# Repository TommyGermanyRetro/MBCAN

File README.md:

# MBCAN

Herzlich willkommen auf meinen GITHUB-Seiten zum Projekt "MBCAN". Bis Ende 2025 hatte ich noch eine Website mit allen Infos rund um das Projekt. Die Pflege war aber mehr als aufwändig, und so habe ich sie geschlossen. Außerdem war das Projekt zu diesem Zeitpunkt bereits 18 Jahre alt. Also Zeit, es abzuschließen und Neues auszuprobieren.

Damit der letzte Stand der Unterlagen nicht verloren geht, habe ich:

1) Alle Unterlagen inkl. Quellcodes an Jörg Seitz übergeben (https://www.jss-elektronik.de)

2) Ein eigenes Git erstellt, auf dem die Downloads der ehemaligen Website abgelegt sind (<a href="https://github.com/TommyGermanyRetro/MBCAN/tree/main/Generation_3">Generation_3 hier im Git</a>)

Durch die Beschäftigung mit moderneren Prozessoren wie ESP32 und RP2040 habe ich neue Motivation für das Projekt gefunden und portiere gerade die 3. Generation Arduino IDE tauglich auf die Prozessoren ATMEGA644P (wie bei der 3. Generation), den ESP32-C3, den Waveshare RP2040 Zero und den RP RP2040 Pi Pico. Diese Versionen bezeichne ich als 4. Generation.

Passend gibt es ein erweitertes Parametriercenter, welches auch das Firmwareupdate der neuen Prozessoren über den CAN-Bus ermöglicht. Dazu wird die OTA-Funktionalität genutzt. Eine reale Umsetzung werde ich für den mbc80 mit dem ESP32-C3 in Eagle erstellen und gleichfalls hier posten. Nur die Bedienungsanleitungen und Warenkörbe, die ich früher mal geschrieben habe, wird es nicht mehr geben.

Solltet ihr Spaß an der Weiterentwicklung auf Basis dieser Sketche haben seid ihr gerne eingeladen, den Sourcecode fleißig zu nutzen und zu experimentieren.

Bleibt gesund,<br>
Thomas

## 1.  Systemarchitekur

Im folgenden Bild ist die Systemarchitektur von MBCAN abgebildet. Der CAN-Bus erfordert eine strikte Linienstruktur. Für Verzweigungen ist ein Hub notwendig zur Sicherstellung der Terminierung des Busses zur Vermeidung von ungewolltem Verhalten.

## 2.  Portierungshistorie

In der nachfolgenden Tabelle sind die bereits portierten (Generation_4/Module) UND getesteten Hardwareversionen und Sketches gelistet. D.h. die für die anderen Prozessoren erstellten Sketches sind Vorschläge ohne echte Überprüfung an einer Hardware. Die Spalte Android nennt Module, die als App auf einem Android-Tablet oder -Smartphone nachgebildet sind (Generation_4/Software/Android).

| Modultyp            | ATMEGA644P          | ESP32C3             | Android             |
| :-----------------: | :-----------------: | :-----------------: | :-----------------: |
| mbc-80              | HW:21-10-01         | HW:26-08-05         |                     |
| mbc-81              | HW:18-02-12<br>HW:24-01-06         |    |                     |
| mbc-82              | HW:21-03-01         |                     |                     |
| mbc-83              | HW:18-02-10<br>HW:24-03-23         |     |                     |
| mbc-84              | HW:18-02-03<br>HW:24-01-06         |      |                     |
| mbc-88              | HW:18-03-29<br>HW:24-01-06         |       |                     |
| mbc-89              | HW:22-03-01         |                     | [mbc89-APP](Generation_4/Software/Android/mbc89_APP) |
| mbc-90              | HW:18-03-04<br>HW:23-11-25         |                     |                     |
| mbc-91              | HW:16-10-02<br>HW:24-04-01         |                     |                     |
| mbc-92              | HW:24-07-20         |                     |                     |
| mbc-93              | HW:24-05-01         |                     |                     |

## 3.  Parametrierungscenter und Tools

Die Module müssen grundsätzlich durch das <b>Parametriercenter</b> basisparametriert werden. Dies bezieht sich auf die GUiD und den Kenner (Abweichungen sind in den Libs beschrieben). Danach ist eine Parametrierung über eine CSx möglich.

Als weiteres Tool steht ein TCP/CAN-Monitor zum Mitlesen auf dem CAN-Bus zur Verfügung.

Beide Tools liegen als Projektmappen in Generation_4/Software/Tools zum Download bereit.
	
## 4.  Lizenz

Soweit nicht ausdrücklich anders angegeben, gelten für dieses Repository folgende Lizenzen (Einzelheiten in [LICENSE.txt](LICENSE.txt)):

| Inhalt | Lizenz |
| --- | --- |
| Software: Sketches, Bibliotheken, Firmware, HEX-Dateien, Parametriercenter, CANMON | [MIT](LICENSE.txt) |
| Hardware: Schaltpläne und Layouts (Eagle), Gerber- und Bohrdaten, Stücklisten, 3D-Druck-Dateien | [CERN-OHL-S-2.0](LICENSE-CERN-OHL-S-2.0.txt) |
| Dokumentation und Bilder: READMEs, Bedienungsanleitungen, Übersichten, Flyer, Fotos | [CC BY-SA 4.0](https://creativecommons.org/licenses/by-sa/4.0/legalcode.de) |

Fremdbestandteile (MightyCore-Dateien, die 8x8-Zeichensatztabelle des SSD1306-Treibers, Arduino-Kerne in den HEX-Dateien) behalten ihre eigenen Lizenzen. Märklin, Central Station, Connect 6021 und Mobile Station sind Marken ihrer Inhaber; MBCAN ist kein Produkt dieser Firmen.

**Haftungsausschluss:** Alle Inhalte dieses Repositorys werden ohne Mängelgewähr ("wie besehen") und ohne jede Gewährleistung bereitgestellt. Nachbau, Anschluss und Nutzung der Hardware und Software erfolgen auf eigene Gefahr. Soweit gesetzlich zulässig, übernimmt der Autor keine Haftung für Schäden an Modellbahnanlagen, Zentralen, Decodern, Fahrzeugen, Rechnern, sonstigen Geräten oder Daten sowie für sonstige Verluste, die aus der Nutzung entstehen. Die Haftungsausschlüsse in [LICENSE.txt](LICENSE.txt) und [LICENSE-CERN-OHL-S-2.0.txt](LICENSE-CERN-OHL-S-2.0.txt) gelten uneingeschränkt.

# Tagebuch

## 07.11.2026

Neu: **mbc89-APP** für Android (Version 1.0.0) unter Generation_4/Software/Android/mbc89_APP mit Quellcode, fertiger APK und Anleitung. Die App bildet das mbc-89 mit Control Unit 6021, Control 80f, Keyboard 6040 und Memory 6043 auf Tablet oder Smartphone nach und verbindet sich per WLAN über einen mbc-80 (ESP32-C3) mit dem CAN-Bus. Hardwaregetestet an einer CS3, auch mit zwei Geräten gleichzeitig.

MBCANLib 1.1.2 / Mbc89Lib 1.1.1: CAN-Hash nach CS2-Protokoll 2.0 (bisher bekamen Module derselben Art mit Modulnummer #0/#1 denselben Hash). `MbcWifiBridge` sendet nicht mehr blockierend und trennt einen Client, der nichts mehr annimmt, statt durch den Watchdog neu zu starten. Hardwaregetestet mit dem mbc-80 ESP32-C3.

## 04.11.2026

MBCANLib/Mbc80Lib 1.1.1, mbc-80 ESP32-C3 V1.0.2: Nicht blockierender TWAI-Versand (`MbcCan`-Parameter `nonBlockingTx`, nur beim mbc-80 gesetzt). Damit meldet sich ein Android-Tablet-Modul über die CAN-TCP-Bridge des mbc-80 auch ohne MBCAN-Teilnehmer an der CS3 mit allen 76 Konfigkanälen an; vorher bremste der blockierende Versand die Bridge. Hardwaregetestet.

## 03.11.2026

MBCANLib/Mbc80Lib 1.1.0, mbc-80 ESP32-C3 V1.0.1: `MbcWifiBridge` nimmt bis zu 3 TCP-Clients gleichzeitig an, z. B. Parametriercenter und Android-Tablet am selben mbc-80. WLAN-Setup-Webportal zentriert. Hardwaregetestet.

## 02.11.2026

Haftungsausschluss im Abschnitt Lizenz ergänzt.

## 22.09.2026

mbc-80 ESP32-C3 (HW:26-08-05) hardwaregetestet und in der Tabelle ergänzt. Außerdem funktioniert das Firmwareupdate per OTA für den ESP32-C3 zuverlässig.

## 31.08.2026

Module mbc82, mbc89 und mbc93 ergänzt. BugFixes und RAM-Optimierung bei den anderen Modulen vorgenommen. 

## 23.08.2026

Unterstützte Hardwareversionen, Bedienungsanleitungen, Informations-MD und portierte Software unter Generation_4 hochgeladen

## 16.08.2026

Erste Bedienungsanleitungen zum neuen Parametriercenter und der portierten Module hochgeladen unter Generation_4/Dokumente

## 13.08.2026

Systemarchitekur ergänzt, Parametriercenter-ZIP unter 3. Generation ergänzt

## 09.08.2026

Neuanlage des Gits zum MBCAN-Projekt

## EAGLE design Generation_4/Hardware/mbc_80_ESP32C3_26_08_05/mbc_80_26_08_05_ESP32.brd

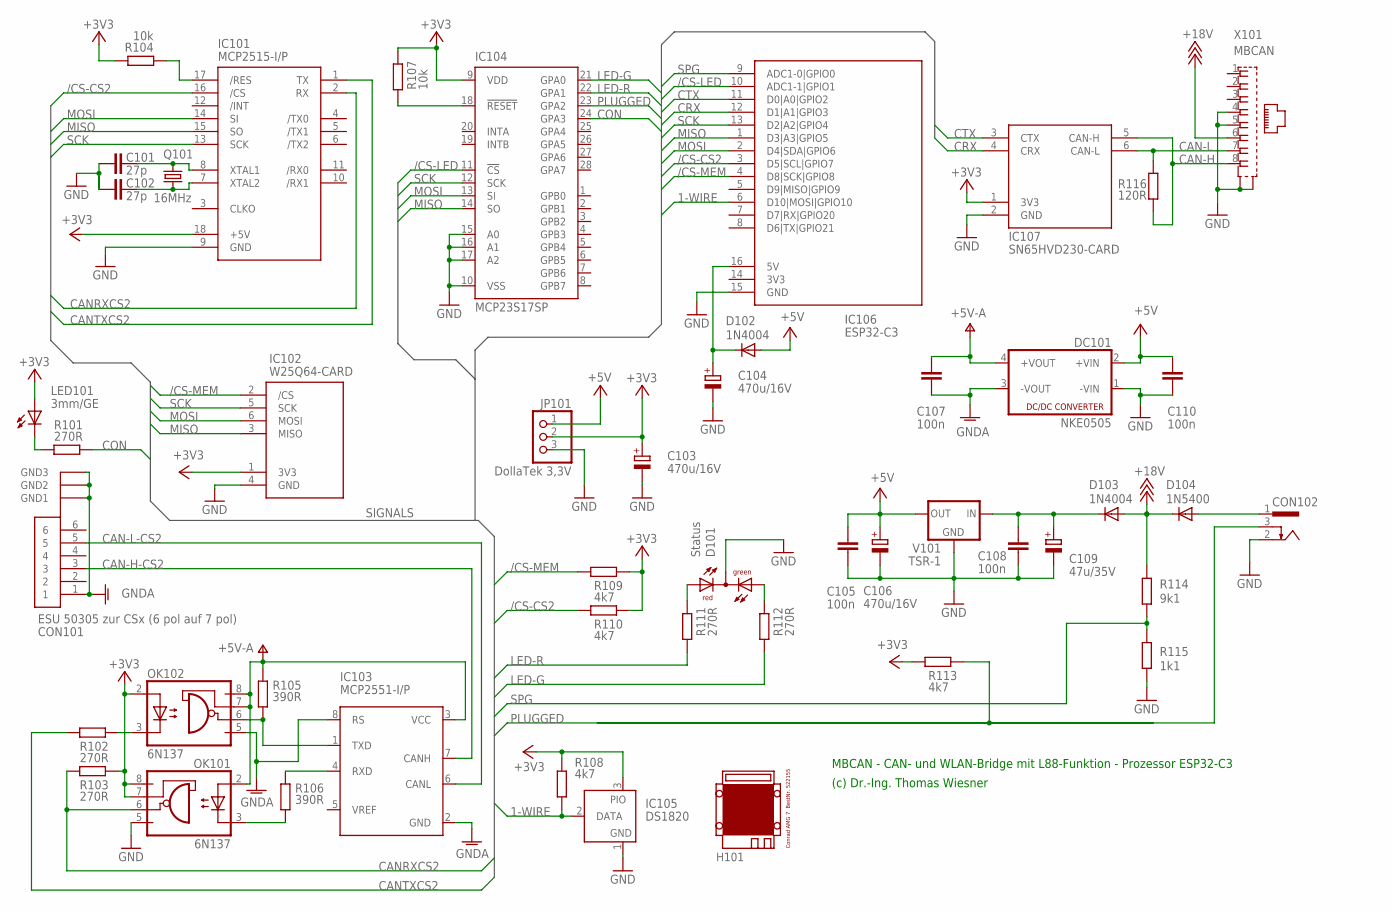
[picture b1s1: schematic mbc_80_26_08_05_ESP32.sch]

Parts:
C101, C102: 27p; C025-025X050
C103, C104, C106: 470u/16V; E3,5-8
C105, C107, C108, C110: 100n; C025-025X050
C109: 47u/35V; E2,5-7
CON101: ESU 50305 zur CSx (6 pol auf 7 pol); MINI-DIN-6-POL
CON102: POWER-JACK
D101: Status; DUOLED5MM
D102, D103: 1N4004; DO41-10
D104: 1N5400; DO201-15
DC101: NKE0505; NME
H101: MODULGEHÄUSE-AMG-7
IC101: MCP2515-I/P; DIL18
IC102: W25Q64-CARD; W25Q64CARD
IC103: MCP2551-I/P; DIL08
IC104: MCP23S17SP; DIL28-3
IC105: DS1820; TO92-
IC106: ESP32-C3
IC107: SN65HVD230-CARD
JP101: DollaTek 3,3V; 1X03
LED101: 3mm/GE; LED3MM
OK101, OK102: 6N137; DIL08
Q101: 16MHz; HC49U-V
R101, R102, R103, R111, R112: 270R; 0207/10
R104, R107: 10k; 0207/10
R105, R106: 390R; 0207/10
R108, R109, R110, R113: 4k7; 0207/10
R114: 9k1; 0207/10
R115: 1k1; 0207/10
R116: 120R; 0207/10
V101: TSR-1; TRACO-TSR-1
X101: MBCAN; 0446200002

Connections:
1-WIRE: IC105.2 (DATA), IC106.6 (D10|MOSI|GPIO10), R108.1
+3V3: C103.+, IC101.18 (+5V), IC102.1 (3V3), IC104.9 (VDD), IC105.3 (PIO), IC107.1 (3V3), JP101.2, LED101.A, OK101.7 (VE), OK101.8 (VCC), OK102.2 (A), R103.2, R104.1, R107.1, R108.2, R109.2, R110.2, R113.1
+5V: C105.1, C106.+, C110.1, D102.A, DC101.2 (+VIN), JP101.1, V101.OUT
+5V-A: C107.1, DC101.4 (+VOUT), IC103.3 (VCC), OK101.2 (A), OK102.7 (VE), OK102.8 (VCC), R105.2
+18V: D103.A, D104.C, R114.1, X101.6
/CS-CS2: IC101.16 (/CS), IC106.3 (D5|SCL|GPIO7), R110.1
/CS-LED: IC104.11 (!CS), IC106.10 (ADC1-1|GPIO1)
/CS-MEM: IC102.2 (/CS), IC106.4 (D8|SCK|GPIO8), R109.1
CAN-H: IC107.5 (CAN-H), R116.1, X101.8
CAN-H-CS2: CON101.3, IC103.7 (CANH)
CAN-L: IC107.6 (CAN-L), R116.2, X101.7
CAN-L-CS2: CON101.5, IC103.6 (CANL)
CANRXCS2: IC101.2 (RX), OK101.6 (VO), R103.1
CANTXCS2: IC101.1 (TX), R102.2
CON: IC104.24 (GPA3), R101.1
CRX: IC106.12 (D1|A1|GPIO3), IC107.4 (CRX)
CTX: IC106.11 (D0|A0|GPIO2), IC107.3 (CTX)
GND: C101.2, C102.2, C103.-, C104.-, C105.2, C106.-, C108.2, C109.-, C110.2, CON102.2, D101.K (C), DC101.1 (-VIN), IC101.9 (GND), IC102.4 (GND), IC104.10 (VSS), IC104.15 (A0), IC104.16 (A1), IC104.17 (A2), IC105.1 (GND), IC106.15 (GND), IC107.2 (GND), JP101.3, OK101.5 (GND), R115.2, V101.GND, X101.4, X101.5, X101.S@1 (S1), X101.S@2 (S2)
GNDA: C107.2, CON101.1, CON101.A1 (GND1), CON101.A2 (GND2), CON101.A3 (GND3), DC101.3 (-VOUT), IC103.2 (GND), IC103.8 (RS), OK102.5 (GND)
LED-G: IC104.21 (GPA0), R112.1
LED-R: IC104.22 (GPA1), R111.1
MISO: IC101.15 (SO), IC102.3 (MISO), IC104.14 (SO), IC106.1 (D3|A3|GPIO5)
MOSI: IC101.14 (SI), IC102.6 (MOSI), IC104.13 (SI), IC106.2 (D4|SDA|GPIO6)
unnamed: IC104.18 (!RESET), R107.2
unnamed: IC101.17 (/RES), R104.2
unnamed: LED101.K (C), R101.2
unnamed: C108.1, C109.+, D103.C, V101.IN
unnamed: C101.1, IC101.8 (XTAL1), Q101.2
unnamed: C102.1, IC101.7 (XTAL2), Q101.1
unnamed: D101.AR, R111.2
unnamed: D101.AG, R112.2
unnamed: C104.+, D102.C, IC106.16 (5V)
unnamed: IC103.1 (TXD), OK102.6 (VO), R105.1
unnamed: OK101.3 (C), R106.1
unnamed: IC103.4 (RXD), R106.2
unnamed: OK102.3 (C), R102.1
PLUGGED: CON102.3, IC104.23 (GPA2), R113.2
SCK: IC101.13 (SCK), IC102.5 (SCK), IC104.12 (SCK), IC106.13 (D2|A2|GPIO4)
SPG: IC106.9 (ADC1-0|GPIO0), R114.2, R115.1
V-NETZTEIL: CON102.1, D104.A

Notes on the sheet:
MBCAN - CAN- und WLAN-Bridge mit L88-Funktion - Prozessor ESP32-C3
(c) Dr.-Ing. Thomas Wiesner

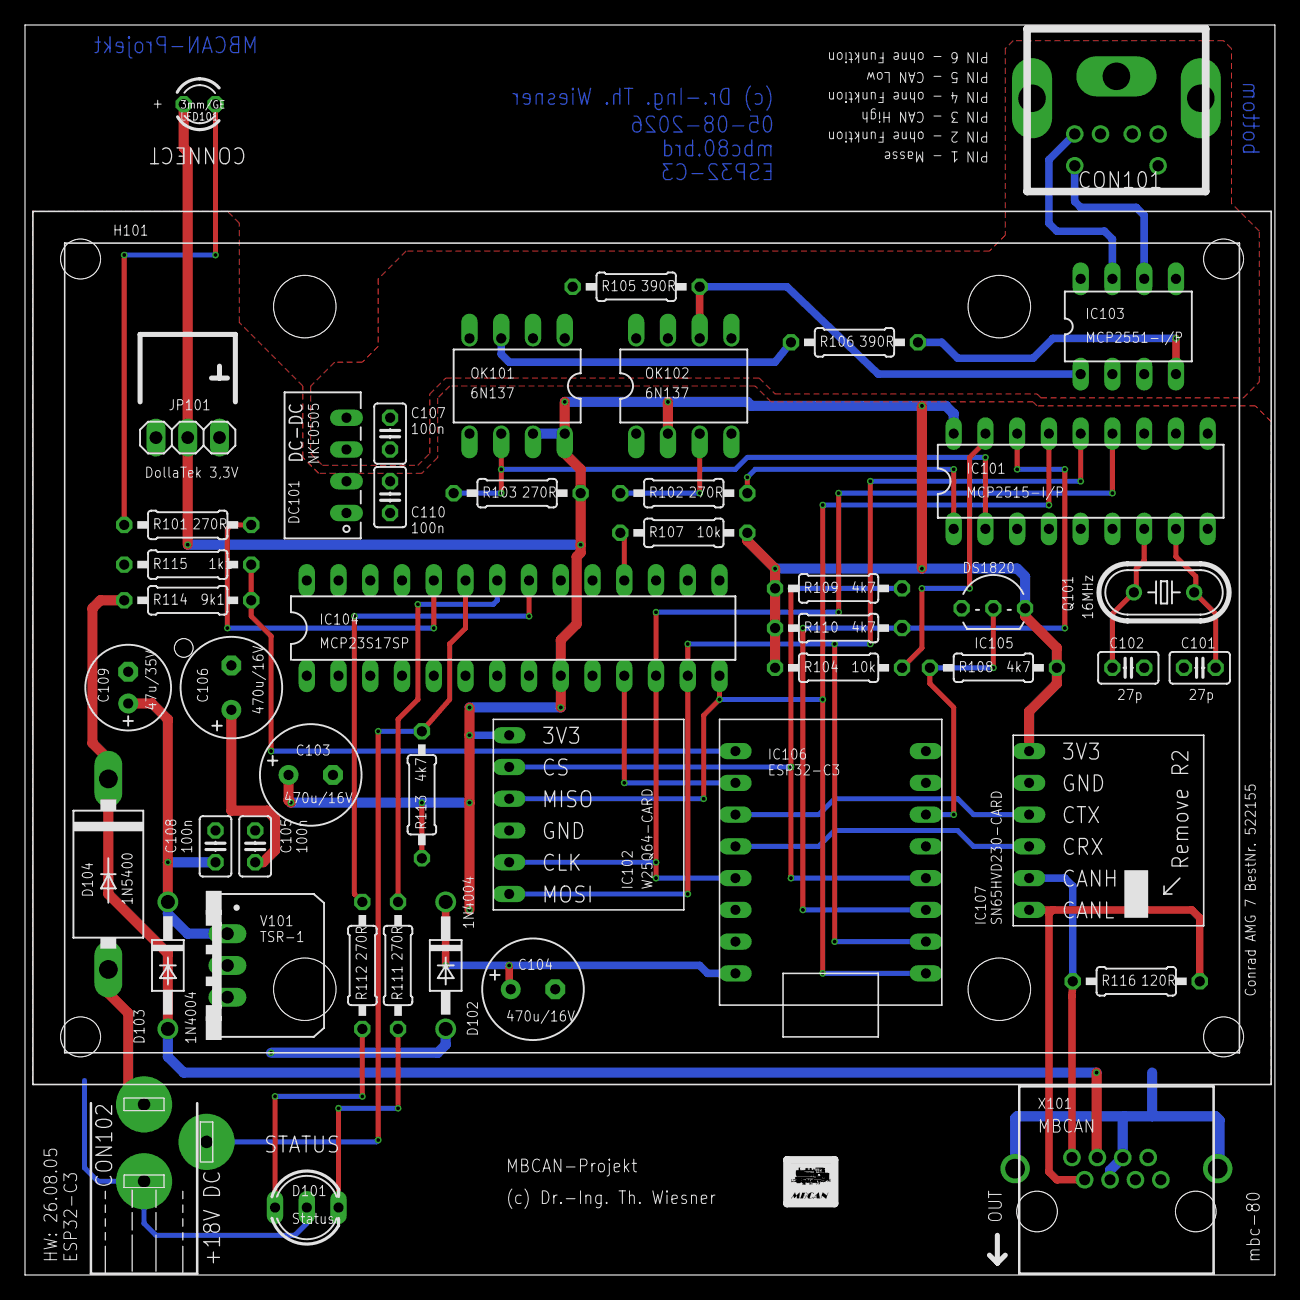
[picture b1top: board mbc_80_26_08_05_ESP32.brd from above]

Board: 2 copper layers, 100.0 x 100.0 mm, 48 parts (0 on the bottom side), 40 nets.

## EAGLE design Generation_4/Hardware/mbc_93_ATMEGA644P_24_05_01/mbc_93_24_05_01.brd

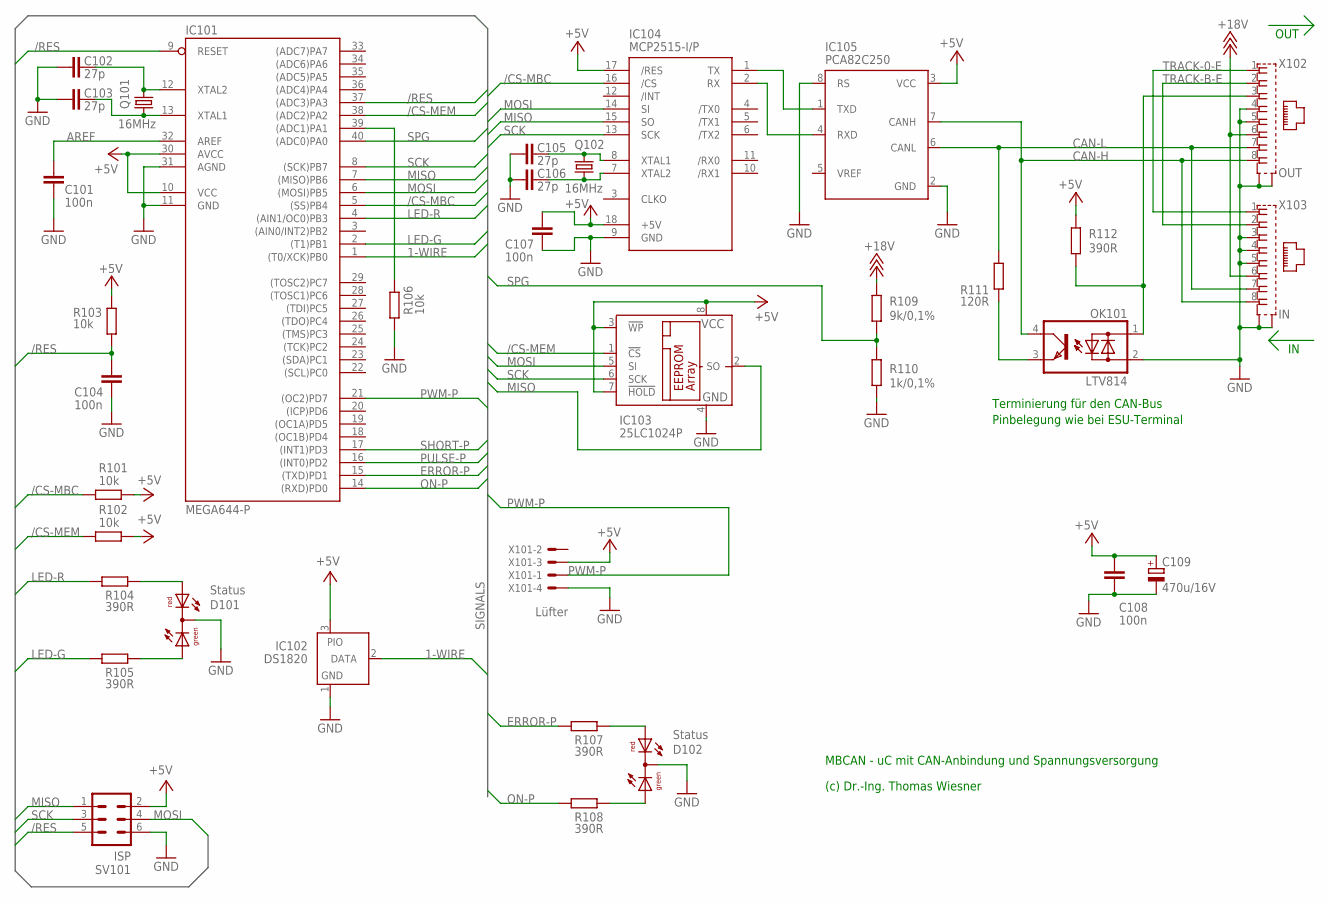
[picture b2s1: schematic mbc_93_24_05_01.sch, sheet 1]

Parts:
C101, C104, C107, C108: 100n; C025-025X050
C102, C103, C105, C106: 27p; C025-025X050
C109: 470u/16V; E3,5-8
D101, D102: Status; DUOLED5MM
IC101: MEGA644-P; DIL40
IC102: DS1820; TO92-
IC103: 25LC1024P; DIL8
IC104: MCP2515-I/P; DIL18
IC105: PCA82C250; DIL08
OK101: LTV814; DIL04
Q101, Q102: 16MHz; HC49U-V
R101, R102, R103, R106: 10k; 0207/10
R104, R105, R107, R108, R112: 390R; 0207/10
R109: 9k/0,1%; 0207/10
R110: 1k/0,1%; 0207/10
R111: 120R; 0207/10
SV101: ISP; ML6
X101: Lüfter; 22-23-2041
X102: OUT; 0446200002
X103: IN; 0446200002

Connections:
1-WIRE: IC101.1 ((T0/XCK)PB0), IC102.2 (DATA)
+5V: C107.1, C108.1, C109.+, IC101.10 (VCC), IC101.30 (AVCC), IC102.3 (PIO), IC103.3 (!WP), IC103.7 (!HOLD), IC103.8 (VCC), IC104.17 (/RES), IC104.18 (+5V), IC105.3 (VCC), R101.2, R102.1, R103.2, R112.1, SV101.2, X101.3; also elsewhere on the board
+18V: R109.1, X102.6, X103.6
/CS-MBC: IC101.5 ((SS)PB4), IC104.16 (/CS), R101.1
/CS-MEM: IC101.38 ((ADC2)PA2), IC103.1 (!CS), R102.2
/RES: C104.1, IC101.9 (RESET), IC101.37 ((ADC3)PA3), R103.1, SV101.5
AREF: C101.1, IC101.32 (AREF)
CAN-H: IC105.7 (CANH), OK101.4 (C), X102.8, X103.8
CAN-L: IC105.6 (CANL), R111.2, X102.7, X103.7
ERROR-P: IC101.15 ((TXD)PD1), R107.1
GND: C101.2, C102.2, C103.2, C104.2, C105.2, C106.2, C107.2, C108.2, C109.-, D101.K (C), D102.K (C), IC101.11 (GND), IC101.31 (AGND), IC102.1 (GND), IC103.4 (GND), IC104.9 (GND), IC105.2 (GND), IC105.8 (RS), OK101.2 (AC2), R106.1, R110.2, SV101.6, X101.4, X102.4, X102.5, X102.S@1 (S1), X102.S@2 (S2), X103.3, X103.4, X103.5, X103.S@1 (S1), X103.S@2 (S2); also elsewhere on the board
LED-G: IC101.2 ((T1)PB1), R105.1
LED-R: IC101.4 ((AIN1/OC0)PB3), R104.1
MISO: IC101.7 ((MISO)PB6), IC103.2 (SO), IC104.15 (SO), SV101.1
MOSI: IC101.6 ((MOSI)PB5), IC103.5 (SI), IC104.14 (SI), SV101.4
unnamed: C103.1, IC101.13 (XTAL1), Q101.1
unnamed: C102.1, IC101.12 (XTAL2), Q101.2
unnamed: C105.1, IC104.8 (XTAL1), Q102.2
unnamed: C106.1, IC104.7 (XTAL2), Q102.1
unnamed: IC101.39 ((ADC1)PA1), R106.2
unnamed: D101.AR, R104.2
unnamed: D101.AG, R105.2
unnamed: IC104.1 (TX), IC105.1 (TXD)
unnamed: IC104.2 (RX), IC105.4 (RXD)
unnamed: OK101.3 (E), R111.1
unnamed: OK101.1 (AC1), R112.2, X102.3
unnamed: D102.AR, R107.2
unnamed: D102.AG, R108.2
ON-P: IC101.14 ((RXD)PD0), R108.1; also elsewhere on the board
PULSE-P: IC101.16 ((INT0)PD2); also elsewhere on the board
PWM-P: IC101.21 ((OC2)PD7), X101.1
SCK: IC101.8 ((SCK)PB7), IC103.6 (SCK), IC104.13 (SCK), SV101.3
SHORT-P: IC101.17 ((INT1)PD3); also elsewhere on the board
SPG: IC101.40 ((ADC0)PA0), R109.2, R110.1
TRACK-0-E: X102.1, X103.1; also elsewhere on the board
TRACK-B-E: X102.2, X103.2; also elsewhere on the board

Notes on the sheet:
MBCAN - uC mit CAN-Anbindung und Spannungsversorgung
(c) Dr.-Ing. Thomas Wiesner
Terminierung für den CAN-Bus
Pinbelegung wie bei ESU-Terminal
OUT

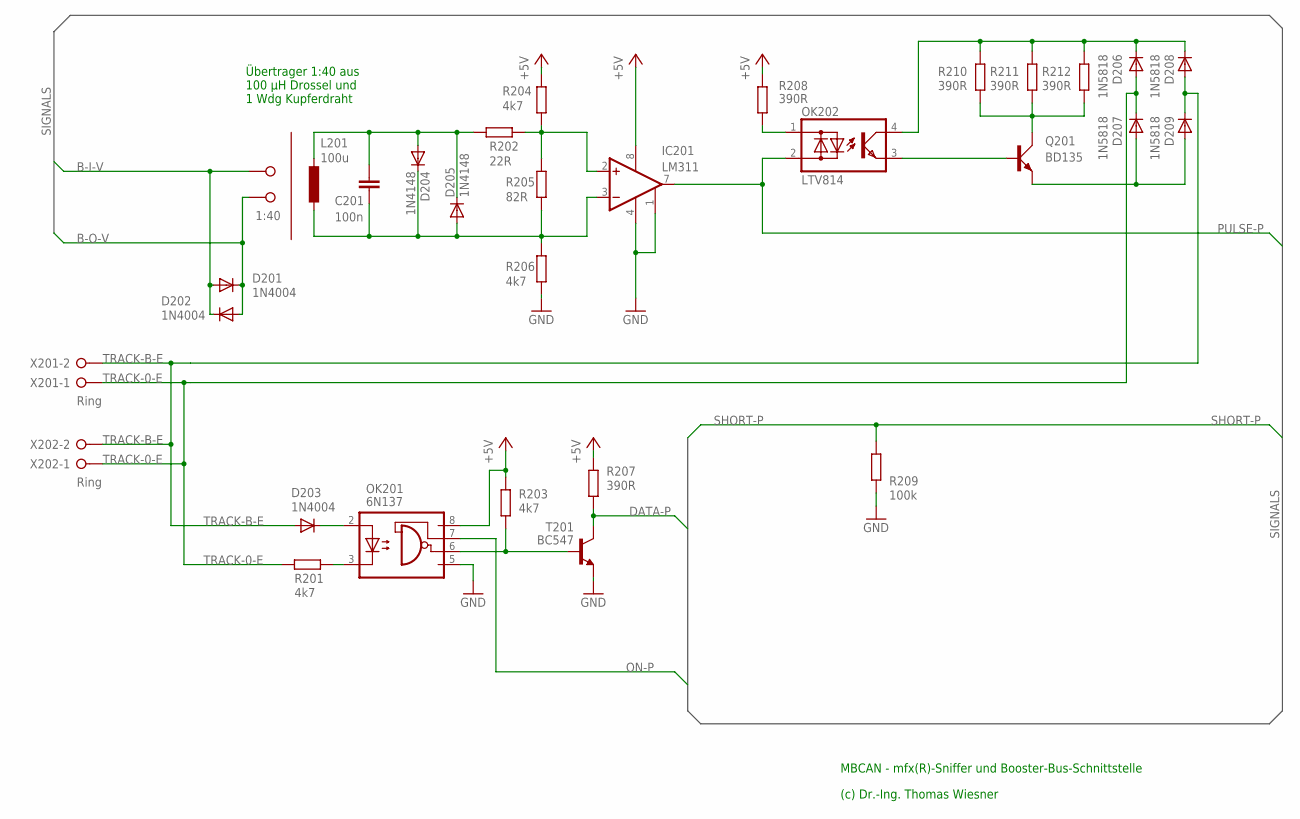
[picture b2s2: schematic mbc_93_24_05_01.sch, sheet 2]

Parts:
C201: 100n; C025-025X050
D201, D202, D203: 1N4004; DO41-10
D204, D205: 1N4148; DO35-10
D206, D207, D208, D209: 1N5818; DO41-10
IC201: LM311; DIL08
L201: 100u; 6000-XXXX-RC
OK201: 6N137; DIL08
OK202: LTV814; DIL04
Q201: BD135; TO126AV
R201, R203, R204, R206: 4k7; 0207/10
R202: 22R; 0207/10
R205: 82R; 0207/10
R207, R208, R210, R211, R212: 390R; 0207/10
R209: 100k; 0207/10
T201: BC547; TO92
TP: 1:40; W237-132
X201, X202: Ring; W237-132

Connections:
+5V: IC201.8 (V+), OK201.8 (VCC), R203.1, R204.2, R207.1, R208.2; also elsewhere on the board
B-I-V: D201.A, D202.C, TP.2; also elsewhere on the board
B-O-V: D201.C, D202.A, TP.1; also elsewhere on the board
DATA-P: R207.2, T201.3 (C); also elsewhere on the board
GND: IC201.1 (EMIOUT), IC201.4 (V-), OK201.5 (GND), R206.2, R209.2, T201.1 (E); also elsewhere on the board
unnamed: D206.C, D208.C, OK202.4 (C), R210.1, R211.1, R212.1
unnamed: D203.C, OK201.2 (A)
unnamed: OK201.3 (C), R201.1
unnamed: C201.1, D204.A, D205.C, L201.1, R202.1
unnamed: OK201.6 (VO), R203.2, T201.2 (B)
unnamed: D207.A, D209.A, Q201.E
unnamed: C201.2, D204.C, D205.A, IC201.3 (-IN), L201.2, R205.2, R206.1
unnamed: IC201.2 (+IN), R202.2, R204.1, R205.1
unnamed: OK202.3 (E), Q201.B
unnamed: Q201.C, R210.2, R211.2, R212.2
unnamed: OK202.1 (AC1), R208.1
ON-P: OK201.7 (VE); also elsewhere on the board
PULSE-P: IC201.7 (COLOUT), OK202.2 (AC2); also elsewhere on the board
SHORT-P: R209.1; also elsewhere on the board
TRACK-0-E: D206.A, D207.C, R201.2, X201.1, X202.1; also elsewhere on the board
TRACK-B-E: D203.A, D208.A, D209.C, X201.2, X202.2; also elsewhere on the board

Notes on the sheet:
Übertrager 1:40 aus 100 µH Drossel und 1 Wdg Kupferdraht
MBCAN - mfx(R)-Sniffer und Booster-Bus-Schnittstelle
(c) Dr.-Ing. Thomas Wiesner

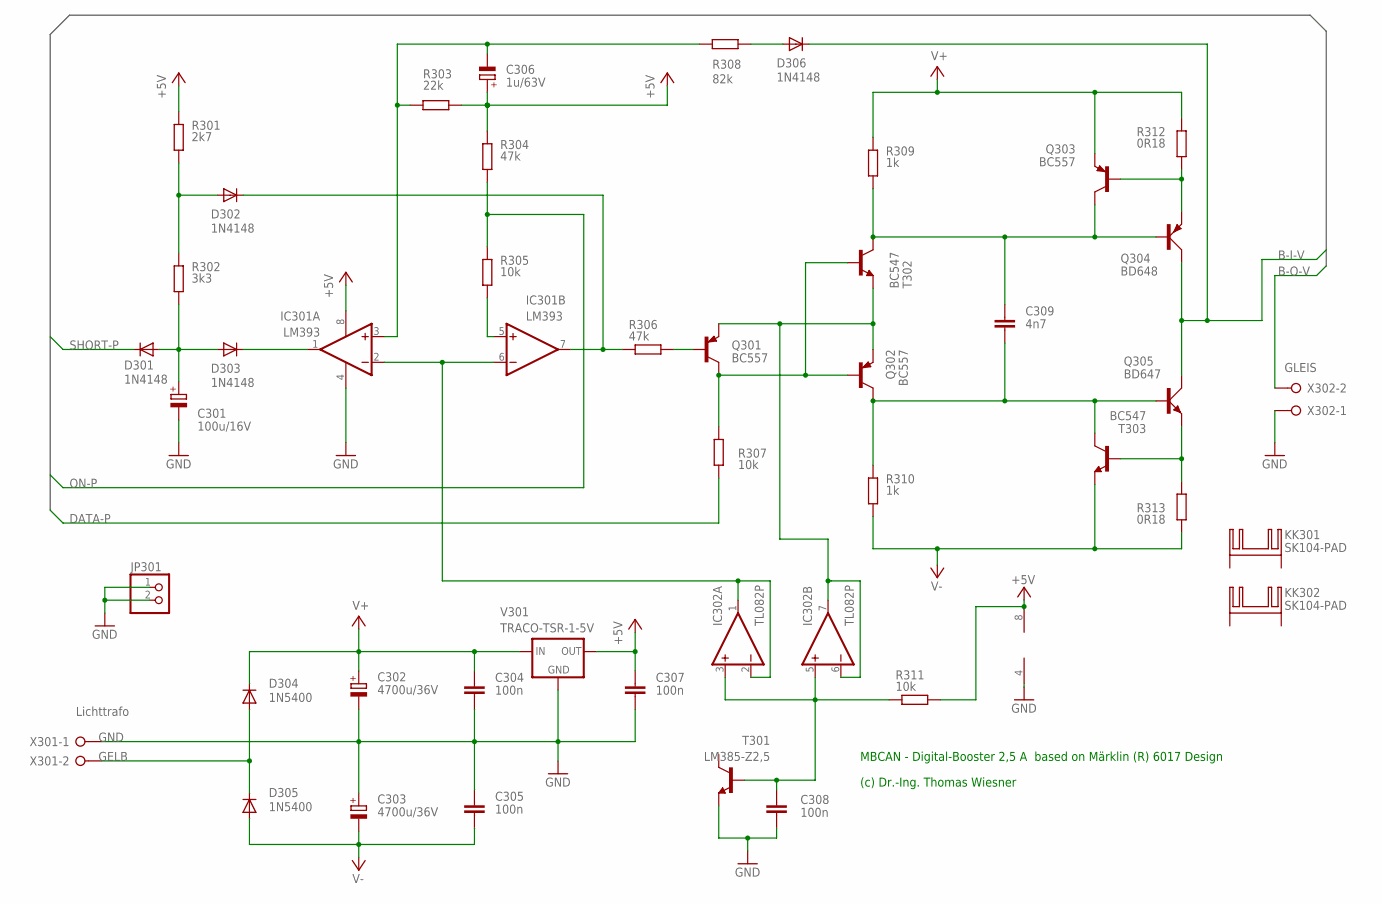
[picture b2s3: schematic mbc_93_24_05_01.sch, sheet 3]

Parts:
C301: 100u/16V; E3,5-8
C302, C303: 4700u/36V; E7,5-16
C304, C305, C307: 100n; C025-024X044
C306: 1u/63V; E2,5-6
C308: 100n; C025-025X050
C309: 4n7; C025-024X044
D301, D302, D303, D306: 1N4148; DO35-7
D304, D305: 1N5400; DO201-15
IC301: LM393; DIL08
IC302: TL082P; DIL08
JP301: PINHD-1X2; 1X02
KK301, KK302: SK104-PAD
Q301, Q302, Q303: BC557; TO92
Q304: BD648; TO220AV
Q305: BD647; TO220AV
R301: 2k7; 0207/10
R302: 3k3; 0207/10
R303: 22k; 0207/10
R304, R306: 47k; 0207/10
R305, R307, R311: 10k; 0207/10
R308: 82k; 0207/10
R309, R310: 1k; 0207/10
R312, R313: 0R18; 0414/15
T301: LM385-Z2,5; TO92
T302, T303: BC547; TO92
V301: TRACO-TSR-1-5V; TRACO-TSR-1
X301: Lichttrafo; W237-132
X302: GLEIS; W237-132

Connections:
+5V: C306.+, C307.1, IC301.8 (V+), IC302.8 (V+), R301.2, R303.1, R304.2, R311.2, V301.OUT; also elsewhere on the board
B-I-V: D306.C, Q304.C, Q305.C; also elsewhere on the board
B-O-V: X302.2; also elsewhere on the board
DATA-P: R307.1; also elsewhere on the board
GELB: D304.A, D305.C, X301.2
GND: C301.-, C302.-, C303.+, C304.2, C305.1, C307.2, C308.2, IC301.4 (V-), IC302.4 (V-), JP301.1, JP301.2, T301.1 (E), V301.GND, X301.1, X302.1; also elsewhere on the board
unnamed: C309.1, Q303.3 (C), Q304.B, R309.1, T302.3 (C)
unnamed: Q303.2 (B), Q304.E, R312.1
unnamed: Q305.E, R313.2, T303.2 (B)
unnamed: C309.2, Q302.3 (C), Q305.B, R310.2, T303.3 (C)
unnamed: C308.1, IC302.3 (+IN), IC302.5 (+IN), R311.1, T301.2 (B)
unnamed: IC301.2 (-IN), IC301.6 (-IN), IC302.1 (OUT), IC302.2 (-IN)
unnamed: IC301.5 (+IN), R305.1
unnamed: IC302.6 (-IN), IC302.7 (OUT), Q301.1 (E), Q302.1 (E), T302.1 (E)
unnamed: Q301.3 (C), Q302.2 (B), R307.2, T302.2 (B)
unnamed: Q301.2 (B), R306.2
unnamed: C306.-, IC301.3 (+IN), R303.2, R308.2
unnamed: D306.A, R308.1
unnamed: D302.C, IC301.7 (COLOUT), R306.1
unnamed: D303.C, IC301.1 (COLOUT)
unnamed: C301.+, D301.A, D303.A, R302.1
unnamed: D302.A, R301.1, R302.2
ON-P: R304.1, R305.2; also elsewhere on the board
SHORT-P: D301.C; also elsewhere on the board
V+: C302.+, C304.1, D304.C, Q303.1 (E), R309.2, R312.2, V301.IN
V-: C303.-, C305.2, D305.A, R310.1, R313.1, T303.1 (E)

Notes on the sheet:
MBCAN - Digital-Booster 2,5 A based on Märklin (R) 6017 Design
(c) Dr.-Ing. Thomas Wiesner

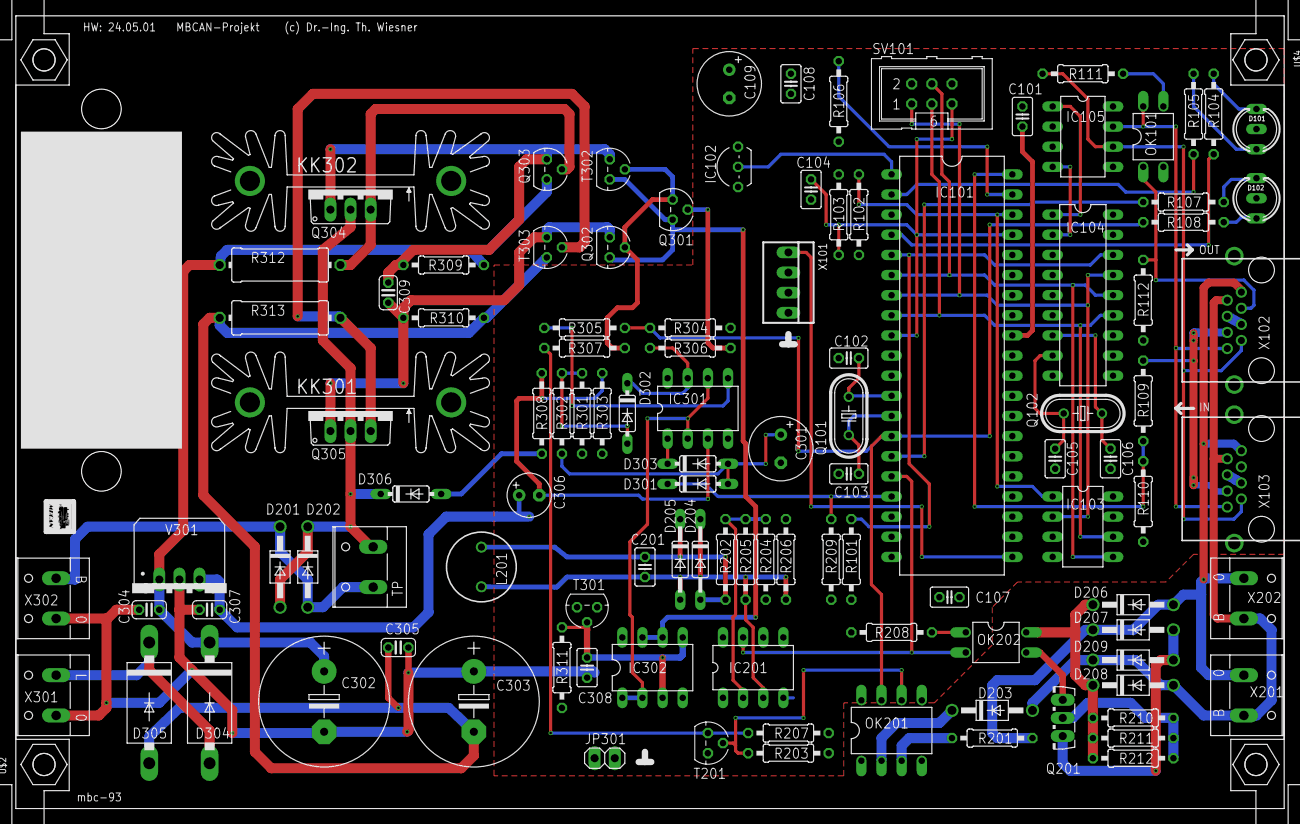
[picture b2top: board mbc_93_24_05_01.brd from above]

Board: 2 copper layers, 160.0 x 100.0 mm, 112 parts (0 on the bottom side), 69 nets.

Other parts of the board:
U$2, U$4: FPH

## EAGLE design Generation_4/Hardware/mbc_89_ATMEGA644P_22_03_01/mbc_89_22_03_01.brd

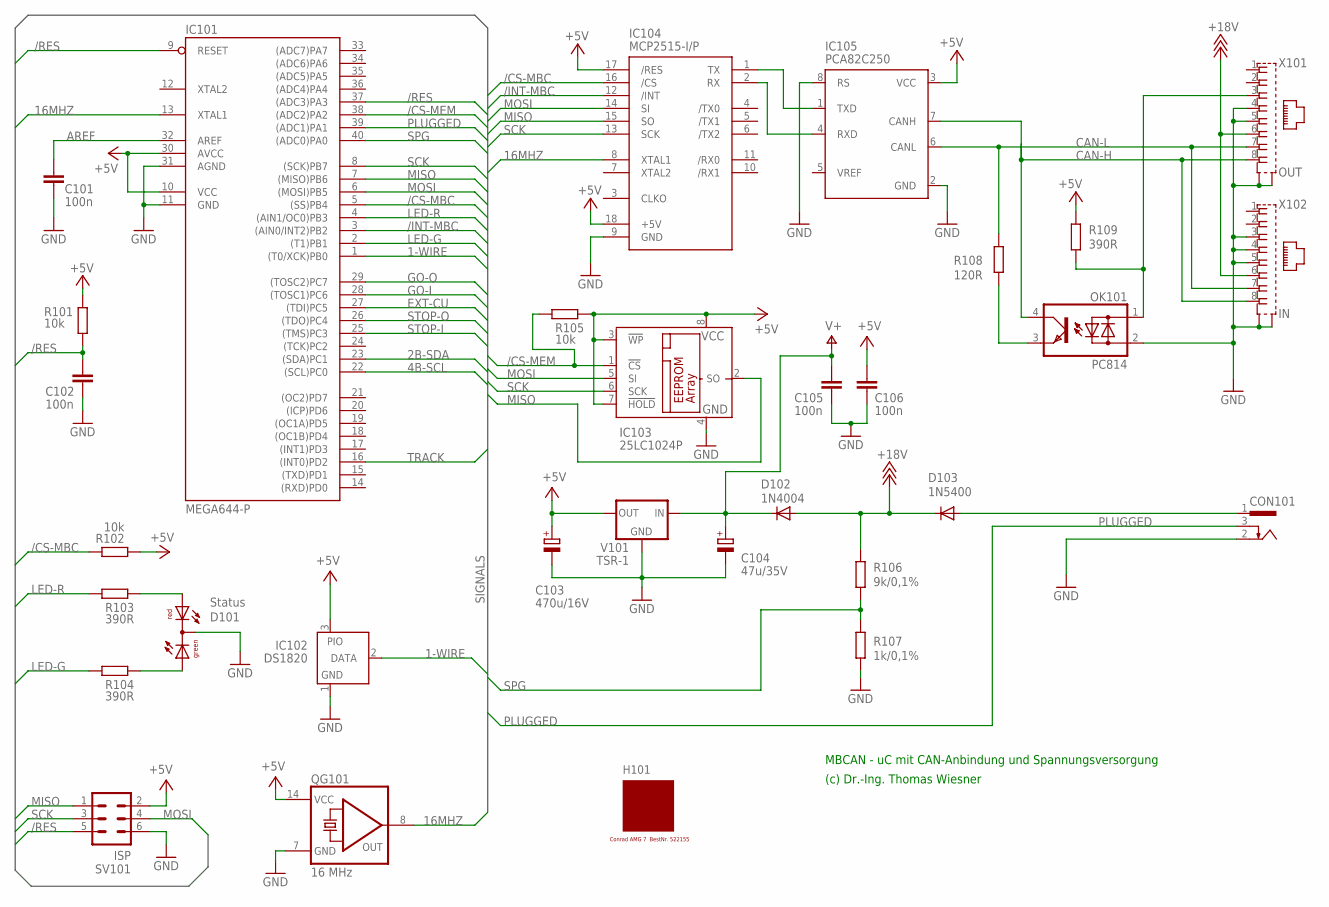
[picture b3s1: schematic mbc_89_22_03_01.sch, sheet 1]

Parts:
C101, C102, C105, C106: 100n; C025-025X050
C103: 470u/16V; E3,5-8
C104: 47u/35V; E2,5-7
CON101: POWER-JACK
D101: Status; DUOLED5MM
D102: 1N4004; DO41-10
D103: 1N5400; DO201-15
H101: MODULGEHÄUSE-AMG-7; MODULGEHÄUSE-1
IC101: MEGA644-P; DIL40
IC102: DS1820; TO92-
IC103: 25LC1024P; DIL8
IC104: MCP2515-I/P; DIL18
IC105: PCA82C250; DIL08
OK101: PC814; DIL04
QG101: 16 MHz; DIL14S
R101, R102, R105: 10k; 0207/10
R103, R104, R109: 390R; 0207/10
R106: 9k/0,1%; 0207/10
R107: 1k/0,1%; 0207/10
R108: 120R; 0207/10
SV101: ISP; ML6
V101: TSR-1; TRACO-TSR-1
X101: OUT; 0446200002
X102: IN; 0446200002

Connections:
1-WIRE: IC101.1 ((T0/XCK)PB0), IC102.2 (DATA)
2B-SDA: IC101.23 ((SDA)PC1); also elsewhere on the board
4B-SCL: IC101.22 ((SCL)PC0); also elsewhere on the board
16MHZ: IC101.13 (XTAL1), IC104.8 (XTAL1), QG101.8 (OUT)
+5V: C103.+, C106.1, IC101.10 (VCC), IC101.30 (AVCC), IC102.3 (PIO), IC103.3 (!WP), IC103.7 (!HOLD), IC103.8 (VCC), IC104.17 (/RES), IC104.18 (+5V), IC105.3 (VCC), QG101.14 (VCC), R101.2, R102.1, R105.2, R109.1, SV101.2, V101.OUT; also elsewhere on the board
+18V: D102.A, D103.C, R106.1, X101.6, X102.6
/CS-MBC: IC101.5 ((SS)PB4), IC104.16 (/CS), R102.2
/CS-MEM: IC101.38 ((ADC2)PA2), IC103.1 (!CS), R105.1
/INT-MBC: IC101.3 ((AIN0/INT2)PB2), IC104.12 (/INT)
/RES: C102.1, IC101.9 (RESET), IC101.37 ((ADC3)PA3), R101.1, SV101.5
AREF: C101.1, IC101.32 (AREF)
CAN-H: IC105.7 (CANH), OK101.4 (C), X101.8, X102.8
CAN-L: IC105.6 (CANL), R108.2, X101.7, X102.7
EXT-CU: IC101.27 ((TDI)PC5); also elsewhere on the board
GND: C101.2, C102.2, C103.-, C104.-, C105.2, C106.2, CON101.2, D101.K (C), IC101.11 (GND), IC101.31 (AGND), IC102.1 (GND), IC103.4 (GND), IC104.9 (GND), IC105.2 (GND), IC105.8 (RS), OK101.2 (AC2), QG101.7 (GND), R107.2, SV101.6, V101.GND, X101.4, X101.5, X101.S@1 (S1), X101.S@2 (S2), X102.3, X102.4, X102.5, X102.S@1 (S1), X102.S@2 (S2); also elsewhere on the board
GO-I: IC101.28 ((TOSC1)PC6); also elsewhere on the board
GO-O: IC101.29 ((TOSC2)PC7); also elsewhere on the board
LED-G: IC101.2 ((T1)PB1), R104.1
LED-R: IC101.4 ((AIN1/OC0)PB3), R103.1
MISO: IC101.7 ((MISO)PB6), IC103.2 (SO), IC104.15 (SO), SV101.1
MOSI: IC101.6 ((MOSI)PB5), IC103.5 (SI), IC104.14 (SI), SV101.4
unnamed: IC104.1 (TX), IC105.1 (TXD)
unnamed: IC104.2 (RX), IC105.4 (RXD)
unnamed: OK101.3 (E), R108.1
unnamed: D101.AR, R103.2
unnamed: OK101.1 (AC1), R109.2, X101.3
unnamed: D101.AG, R104.2
PLUGGED: CON101.3, IC101.39 ((ADC1)PA1)
SCK: IC101.8 ((SCK)PB7), IC103.6 (SCK), IC104.13 (SCK), SV101.3
SPG: IC101.40 ((ADC0)PA0), R106.2, R107.1
STOP-I: IC101.25 ((TMS)PC3); also elsewhere on the board
STOP-O: IC101.26 ((TDO)PC4); also elsewhere on the board
TRACK: IC101.16 ((INT0)PD2); also elsewhere on the board
V+: C104.+, C105.1, D102.C, V101.IN; also elsewhere on the board
V-NETZTEIL: CON101.1, D103.A

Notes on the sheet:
MBCAN - uC mit CAN-Anbindung und Spannungsversorgung
(c) Dr.-Ing. Thomas Wiesner

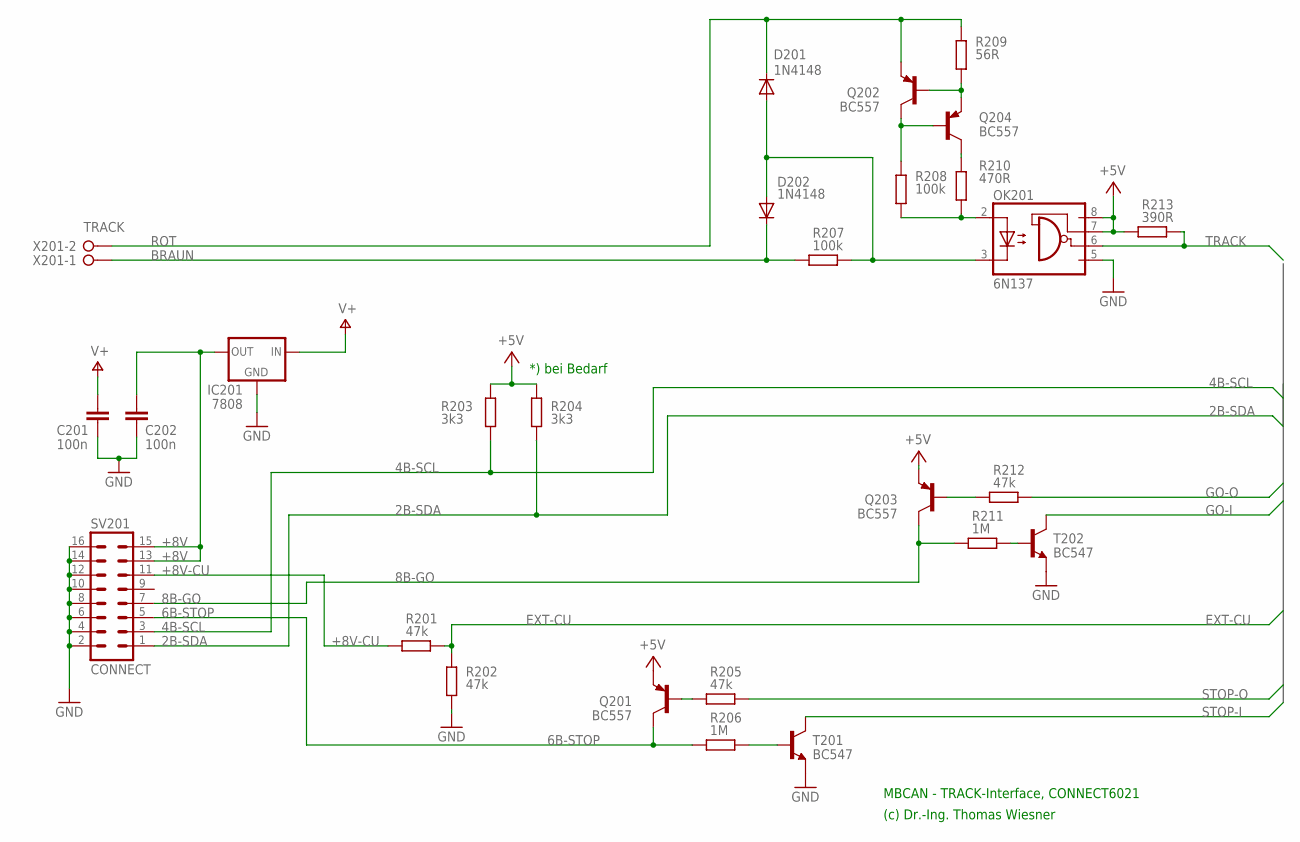
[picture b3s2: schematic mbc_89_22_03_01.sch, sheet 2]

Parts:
C201, C202: 100n; C025-025X050
D201, D202: 1N4148; DO35-10
IC201: 7808; 78XXL
OK201: 6N137; DIL08
Q201, Q202, Q203, Q204: BC557; TO92
R201, R202, R205, R212: 47k; 0207/10
R203, R204: 3k3; 0207/10
R206, R211: 1M; 0207/10
R207, R208: 100k; 0207/10
R209: 56R; 0207/10
R210: 470R; 0207/10
R213: 390R; 0207/10
SV201: CONNECT; ML16
T201, T202: BC547; TO92
X201: TRACK; W237-132

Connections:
2B-SDA: R204.2, SV201.1; also elsewhere on the board
4B-SCL: R203.2, SV201.3; also elsewhere on the board
6B-STOP: Q201.3 (C), R206.2, SV201.5
8B-GO: Q203.3 (C), R211.2, SV201.7
+5V: OK201.7 (VE), OK201.8 (VCC), Q201.1 (E), Q203.1 (E), R203.1, R204.1, R213.1; also elsewhere on the board
+8V: C202.1, IC201.OUT, SV201.13, SV201.15
+8V-CU: R201.2, SV201.11
BRAUN: D202.C, R207.2, X201.1
EXT-CU: R201.1, R202.1; also elsewhere on the board
GND: C201.2, C202.2, IC201.GND, OK201.5 (GND), R202.2, SV201.2, SV201.4, SV201.6, SV201.8, SV201.10, SV201.12, SV201.14, SV201.16, T201.1 (E), T202.1 (E); also elsewhere on the board
GO-I: T202.3 (C); also elsewhere on the board
GO-O: R212.1; also elsewhere on the board
unnamed: R206.1, T201.2 (B)
unnamed: Q201.2 (B), R205.2
unnamed: R211.1, T202.2 (B)
unnamed: Q203.2 (B), R212.2
unnamed: D201.A, D202.A, OK201.3 (C), R207.1
unnamed: Q202.2 (B), Q204.1 (E), R209.2
unnamed: Q202.3 (C), Q204.2 (B), R208.1
unnamed: Q204.3 (C), R210.1
unnamed: OK201.2 (A), R208.2, R210.2
ROT: D201.C, Q202.1 (E), R209.1, X201.2
STOP-I: T201.3 (C); also elsewhere on the board
STOP-O: R205.1; also elsewhere on the board
TRACK: OK201.6 (VO), R213.2; also elsewhere on the board
V+: C201.1, IC201.IN; also elsewhere on the board

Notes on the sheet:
(c) Dr.-Ing. Thomas Wiesner
MBCAN - TRACK-Interface, CONNECT6021
*) bei Bedarf
